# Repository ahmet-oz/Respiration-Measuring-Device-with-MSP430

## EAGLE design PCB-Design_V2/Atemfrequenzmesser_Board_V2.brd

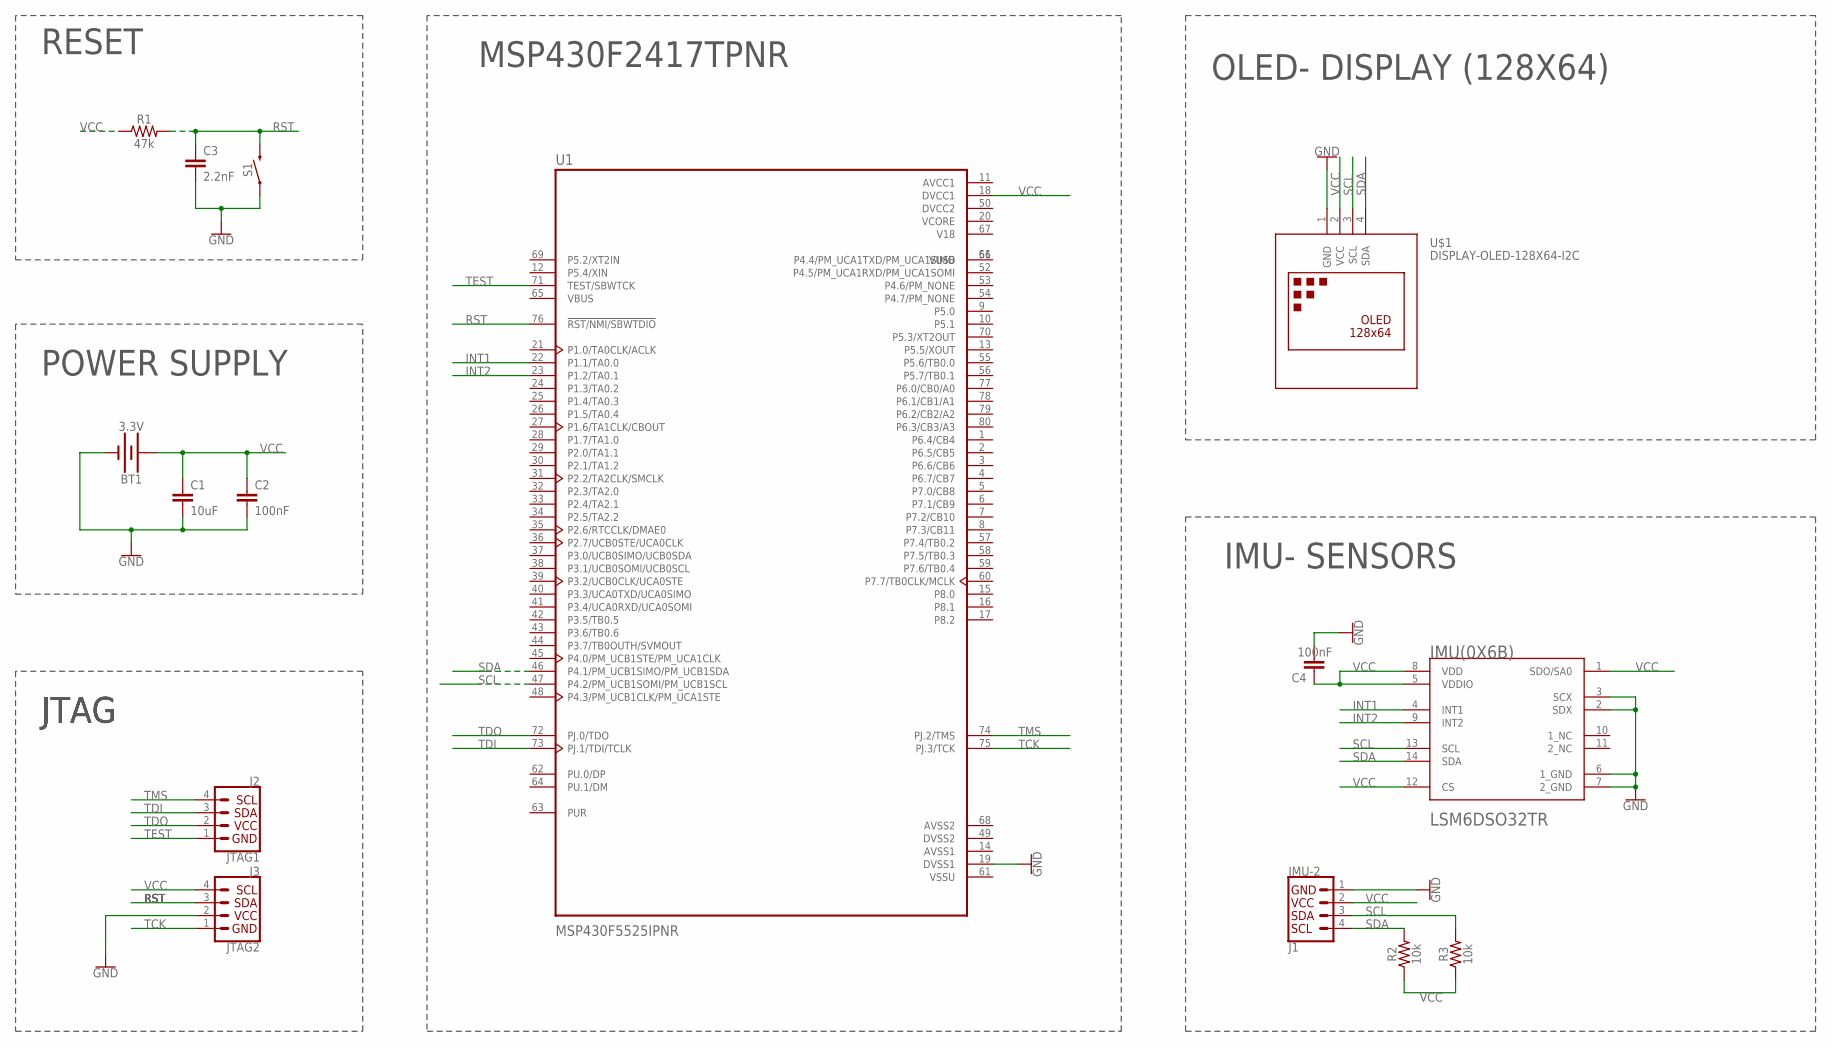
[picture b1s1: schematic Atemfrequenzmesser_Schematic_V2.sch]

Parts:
BT1: 3.3V; BATTCOM_20MM_PTH
C1: 10uF; 0603
C2, C4: 100nF; 0603
C3: 2.2nF; 0603
IMU(0X6B): STMICROELECTRONICS_LSM6DSO32TRSTMICROELECTRONICS_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; STMICROELECTRONICS_LSM6DSO32TR_0
J1: IMU-2; JST04_1MM_RA
J2: JTAG1; JST04_1MM_RA
J3: JTAG2; JST04_1MM_RA
R1: 47k; 0603
R2, R3: 10k; 0603
S1: MOMENTARY-SWITCH-SPST-PTH-6.0MM; TACTILE_SWITCH_PTH_6.0MM
U1: MSP430F5525IPNR; QFP50P1400X1400X160-80N
U$1: DISPLAY-OLED-128X64-I2C

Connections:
AVCC1: U1.11 (AVCC1)
AVSS1: U1.14 (AVSS1)
AVSS2: U1.68 (AVSS2)
DVCC2: U1.50 (DVCC2)
DVSS2: U1.49 (DVSS2)
GND: BT1.2 (-), C1.2, C2.2, C3.2, C4.2, IMU(0X6B).2 (SDX), IMU(0X6B).3 (SCX), IMU(0X6B).6 (1_GND), IMU(0X6B).7 (2_GND), J1.1, J3.2, S1.1, U1.19 (DVSS1), U$1.1 (GND)
INT1: IMU(0X6B).4 (INT1), U1.22 (P1.1/TA0.0)
INT2: IMU(0X6B).9 (INT2), U1.23 (P1.2/TA0.1)
RST: C3.1, J3.3, R1.2, S1.3 (2), U1.76 (!RST/NMI/SBWTDIO)
SCL: IMU(0X6B).13 (SCL), J1.3, R3.2, U1.47 (P4.2/PM_UCB1SOMI/PM_UCB1SCL), U$1.3 (SCL)
SDA: IMU(0X6B).14 (SDA), J1.4, R2.2, U1.46 (P4.1/PM_UCB1SIMO/PM_UCB1SDA), U$1.4 (SDA)
TCK: J3.1, U1.75 (PJ.3/TCK)
TDI: J2.3, U1.73 (PJ.1/TDI/TCLK)
TDO: J2.2, U1.72 (PJ.0/TDO)
TEST: J2.1, U1.71 (TEST/SBWTCK)
TMS: J2.4, U1.74 (PJ.2/TMS)
V18: U1.67 (V18)
VCC: BT1.1 (+), C1.1, C2.1, C4.1, IMU(0X6B).1 (SDO/SA0), IMU(0X6B).5 (VDDIO), IMU(0X6B).8 (VDD), IMU(0X6B).12 (CS), J1.2, J3.4, R1.1, R2.1, R3.1, U1.18 (DVCC1), U$1.2 (VCC)
VCORE: U1.20 (VCORE)
VSSU: U1.61 (VSSU)

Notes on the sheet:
MSP430F2417TPNR
RESET
POWER SUPPLY
JTAG
OLED- DISPLAY (128X64)
IMU- SENSORS

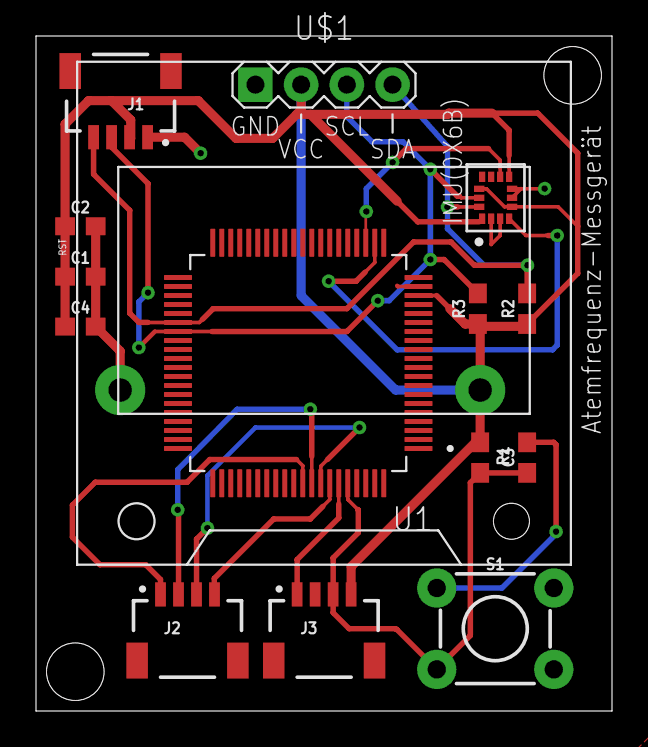
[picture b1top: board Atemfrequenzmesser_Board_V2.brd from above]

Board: 2 copper layers, 32.0 x 37.5 mm, 15 parts (1 on the bottom side), 12 nets.

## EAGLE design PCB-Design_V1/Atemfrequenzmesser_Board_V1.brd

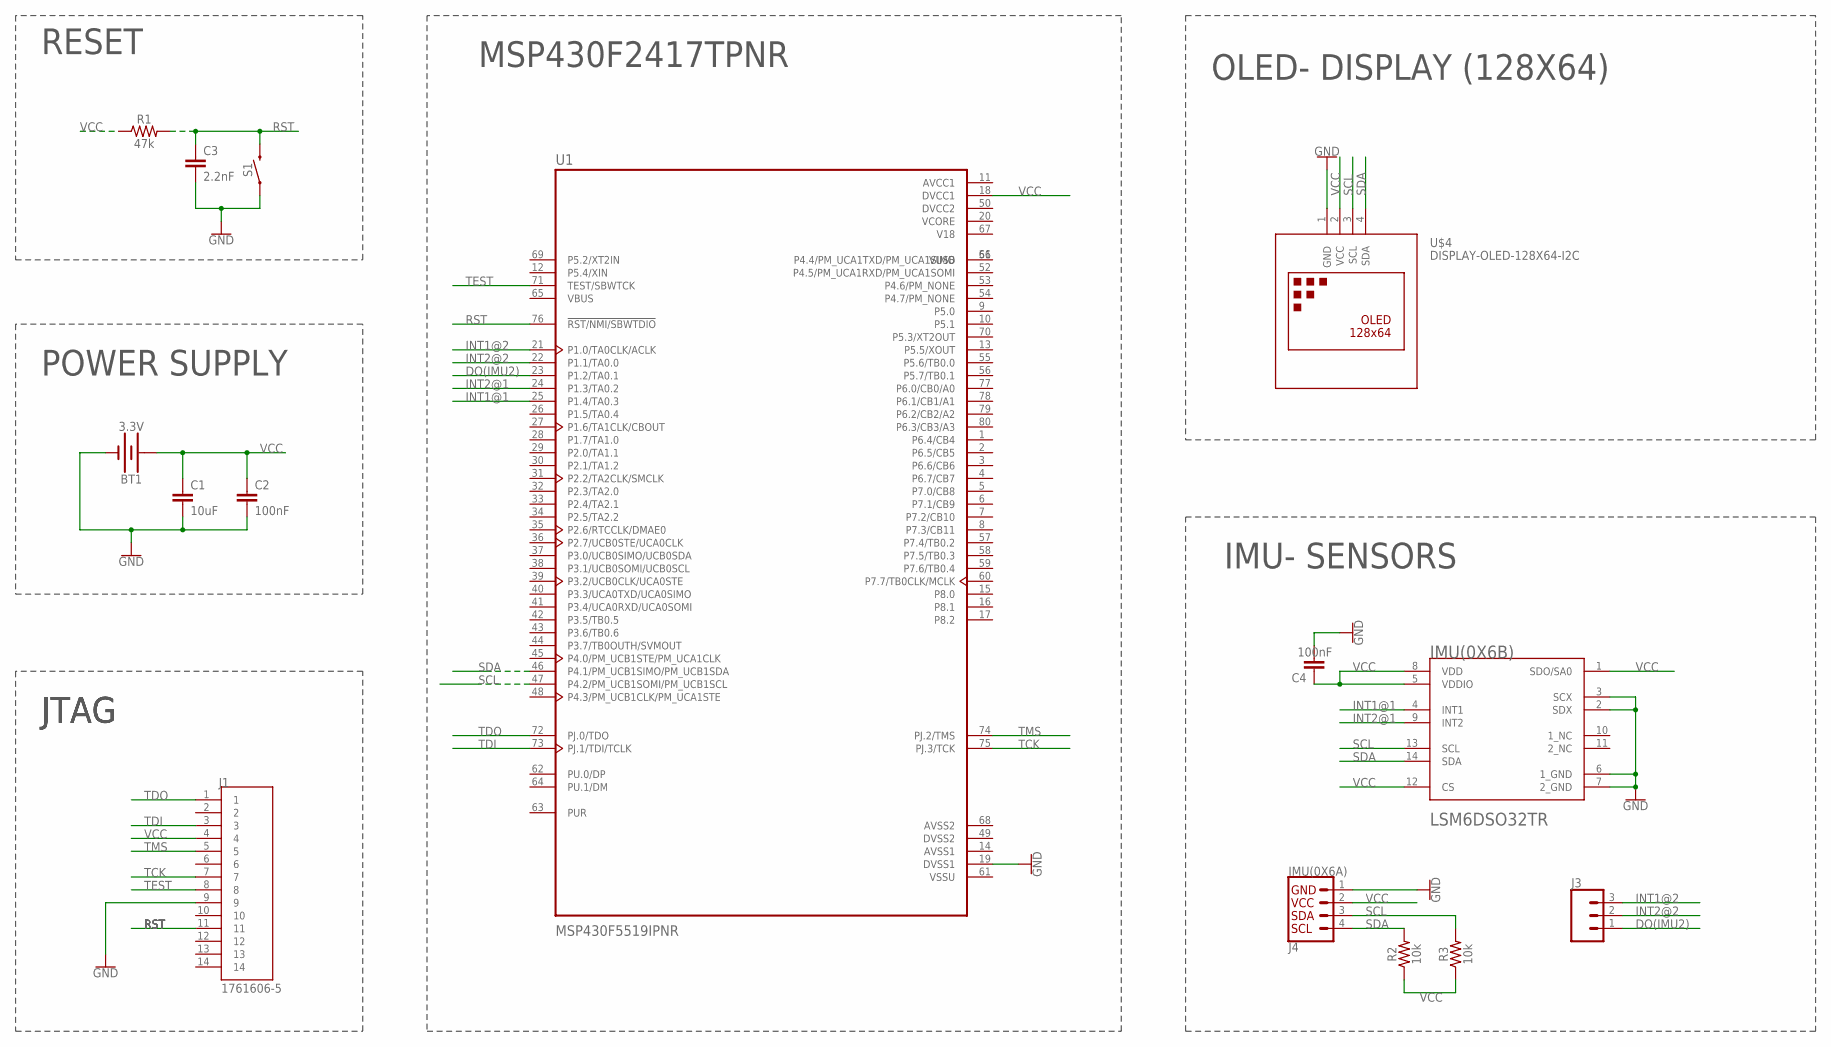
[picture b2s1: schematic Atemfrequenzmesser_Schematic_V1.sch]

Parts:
BT1: 3.3V; BATTCOM_20MM_PTH
C1: 10uF; 0603
C2, C4: 100nF; 0603
C3: 2.2nF; 0603
IMU(0X6B): STMICROELECTRONICS_LSM6DSO32TRSTMICROELECTRONICS_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; STMICROELECTRONICS_LSM6DSO32TR_0
J1: 1761606-5; TE_1761606-5
J3: CONN_03; 1X03
J4: IMU(0X6A); JST04_1MM_RA
R1: 47k; 0603
R2, R3: 10k; 0603
S1: MOMENTARY-SWITCH-SPST-PTH-6.0MM; TACTILE_SWITCH_PTH_6.0MM
U1: MSP430F5519IPNR; QFP50P1400X1400X160-80N
U$4: DISPLAY-OLED-128X64-I2C

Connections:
AVCC1: U1.11 (AVCC1)
AVSS1: U1.14 (AVSS1)
AVSS2: U1.68 (AVSS2)
DO(IMU2): J3.1, U1.23 (P1.2/TA0.1)
DVCC2: U1.50 (DVCC2)
DVSS2: U1.49 (DVSS2)
GND: BT1.2 (-), C1.2, C2.2, C3.2, C4.2, IMU(0X6B).2 (SDX), IMU(0X6B).3 (SCX), IMU(0X6B).6 (1_GND), IMU(0X6B).7 (2_GND), J1.9, J4.1, S1.1, U1.19 (DVSS1), U$4.1 (GND)
INT1@1: IMU(0X6B).4 (INT1), U1.25 (P1.4/TA0.3)
INT1@2: J3.3, U1.21 (P1.0/TA0CLK/ACLK)
INT2@1: IMU(0X6B).9 (INT2), U1.24 (P1.3/TA0.2)
INT2@2: J3.2, U1.22 (P1.1/TA0.0)
RST: C3.1, J1.11, R1.2, S1.3 (2), U1.76 (!RST/NMI/SBWTDIO)
SCL: IMU(0X6B).13 (SCL), J4.3, R3.2, U1.47 (P4.2/PM_UCB1SOMI/PM_UCB1SCL), U$4.3 (SCL)
SDA: IMU(0X6B).14 (SDA), J4.4, R2.2, U1.46 (P4.1/PM_UCB1SIMO/PM_UCB1SDA), U$4.4 (SDA)
TCK: J1.7, U1.75 (PJ.3/TCK)
TDI: J1.3, U1.73 (PJ.1/TDI/TCLK)
TDO: J1.1, U1.72 (PJ.0/TDO)
TEST: J1.8, U1.71 (TEST/SBWTCK)
TMS: J1.5, U1.74 (PJ.2/TMS)
V18: U1.67 (V18)
VCC: BT1.1 (+), C1.1, C2.1, C4.1, IMU(0X6B).1 (SDO/SA0), IMU(0X6B).5 (VDDIO), IMU(0X6B).8 (VDD), IMU(0X6B).12 (CS), J1.4, J4.2, R1.1, R2.1, R3.1, U1.18 (DVCC1), U$4.2 (VCC)
VCORE: U1.20 (VCORE)
VSSU: U1.61 (VSSU)

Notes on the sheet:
MSP430F2417TPNR
RESET
POWER SUPPLY
JTAG
OLED- DISPLAY (128X64)
IMU- SENSORS

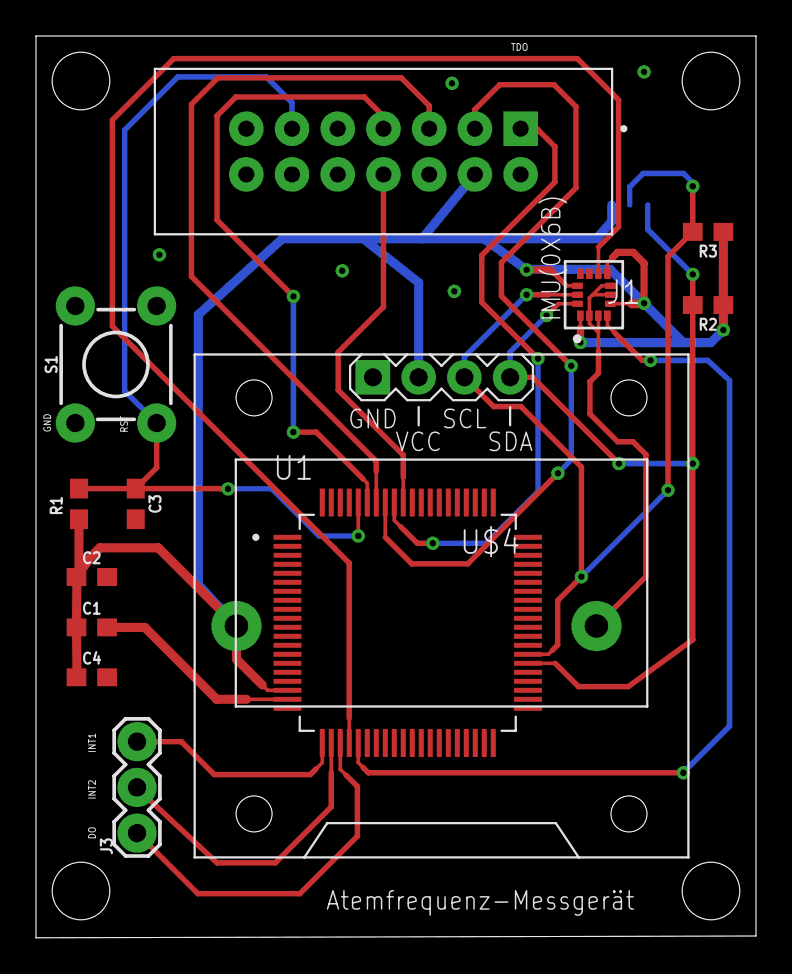
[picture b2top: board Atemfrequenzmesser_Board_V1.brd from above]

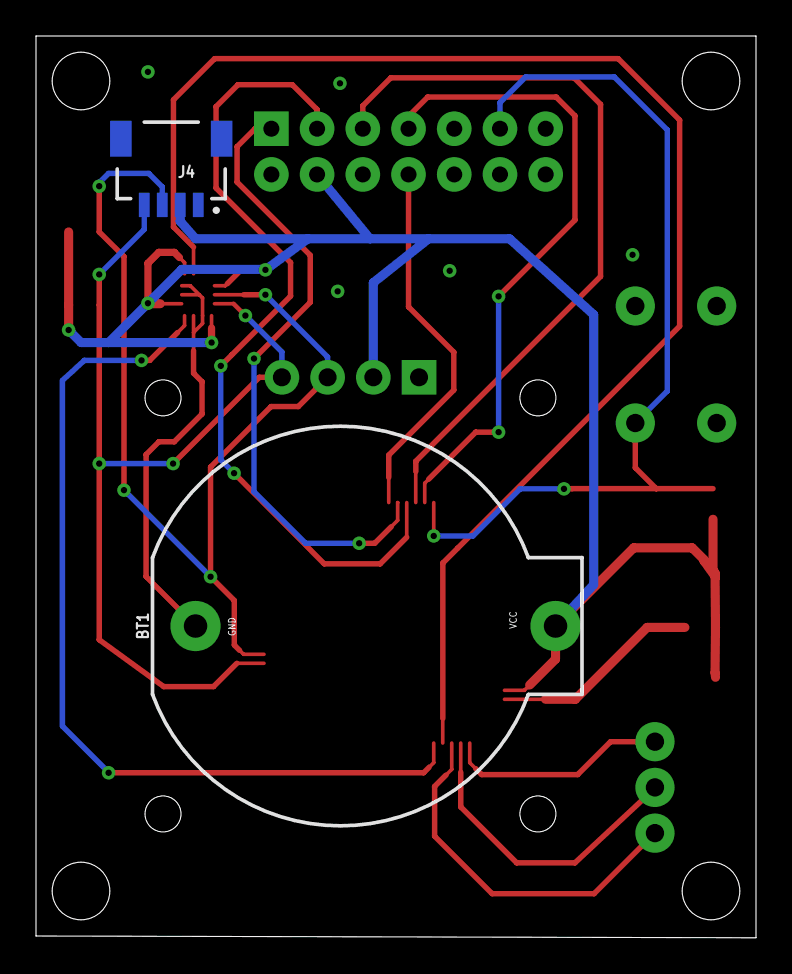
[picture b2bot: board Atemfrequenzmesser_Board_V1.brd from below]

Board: 2 copper layers, 40.0 x 50.1 mm, 15 parts (2 on the bottom side), 15 nets.

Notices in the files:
parts and their libraries:
SparkFun-Capacitors: Licensing: Creative Commons ShareAlike 4.0 International - https://creativecommons.org/licenses/by-sa/4.0
ahmet: Released under the Creative Commons Attribution 4.0 International License: http://creativecommons.org/licenses/by/4.0
